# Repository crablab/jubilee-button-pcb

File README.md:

# jubilee-button-pcb

PCB for the Jubilee Line button replacement PCB. 

Created using KiCad

Check out some sample code here: https://github.com/willfurnell/jubilee-hue

Based on the [original by Will Furnell](https://github.com/willfurnell/jubilee-button-pcb). 

Released under the [MIT Licence](LICENSE). 

You should simply be able to send this off to JLCPCB for manufacture if you wish.

Or, [contact me](mailto:hugh@crablab.uk) as I have some boards already produced.

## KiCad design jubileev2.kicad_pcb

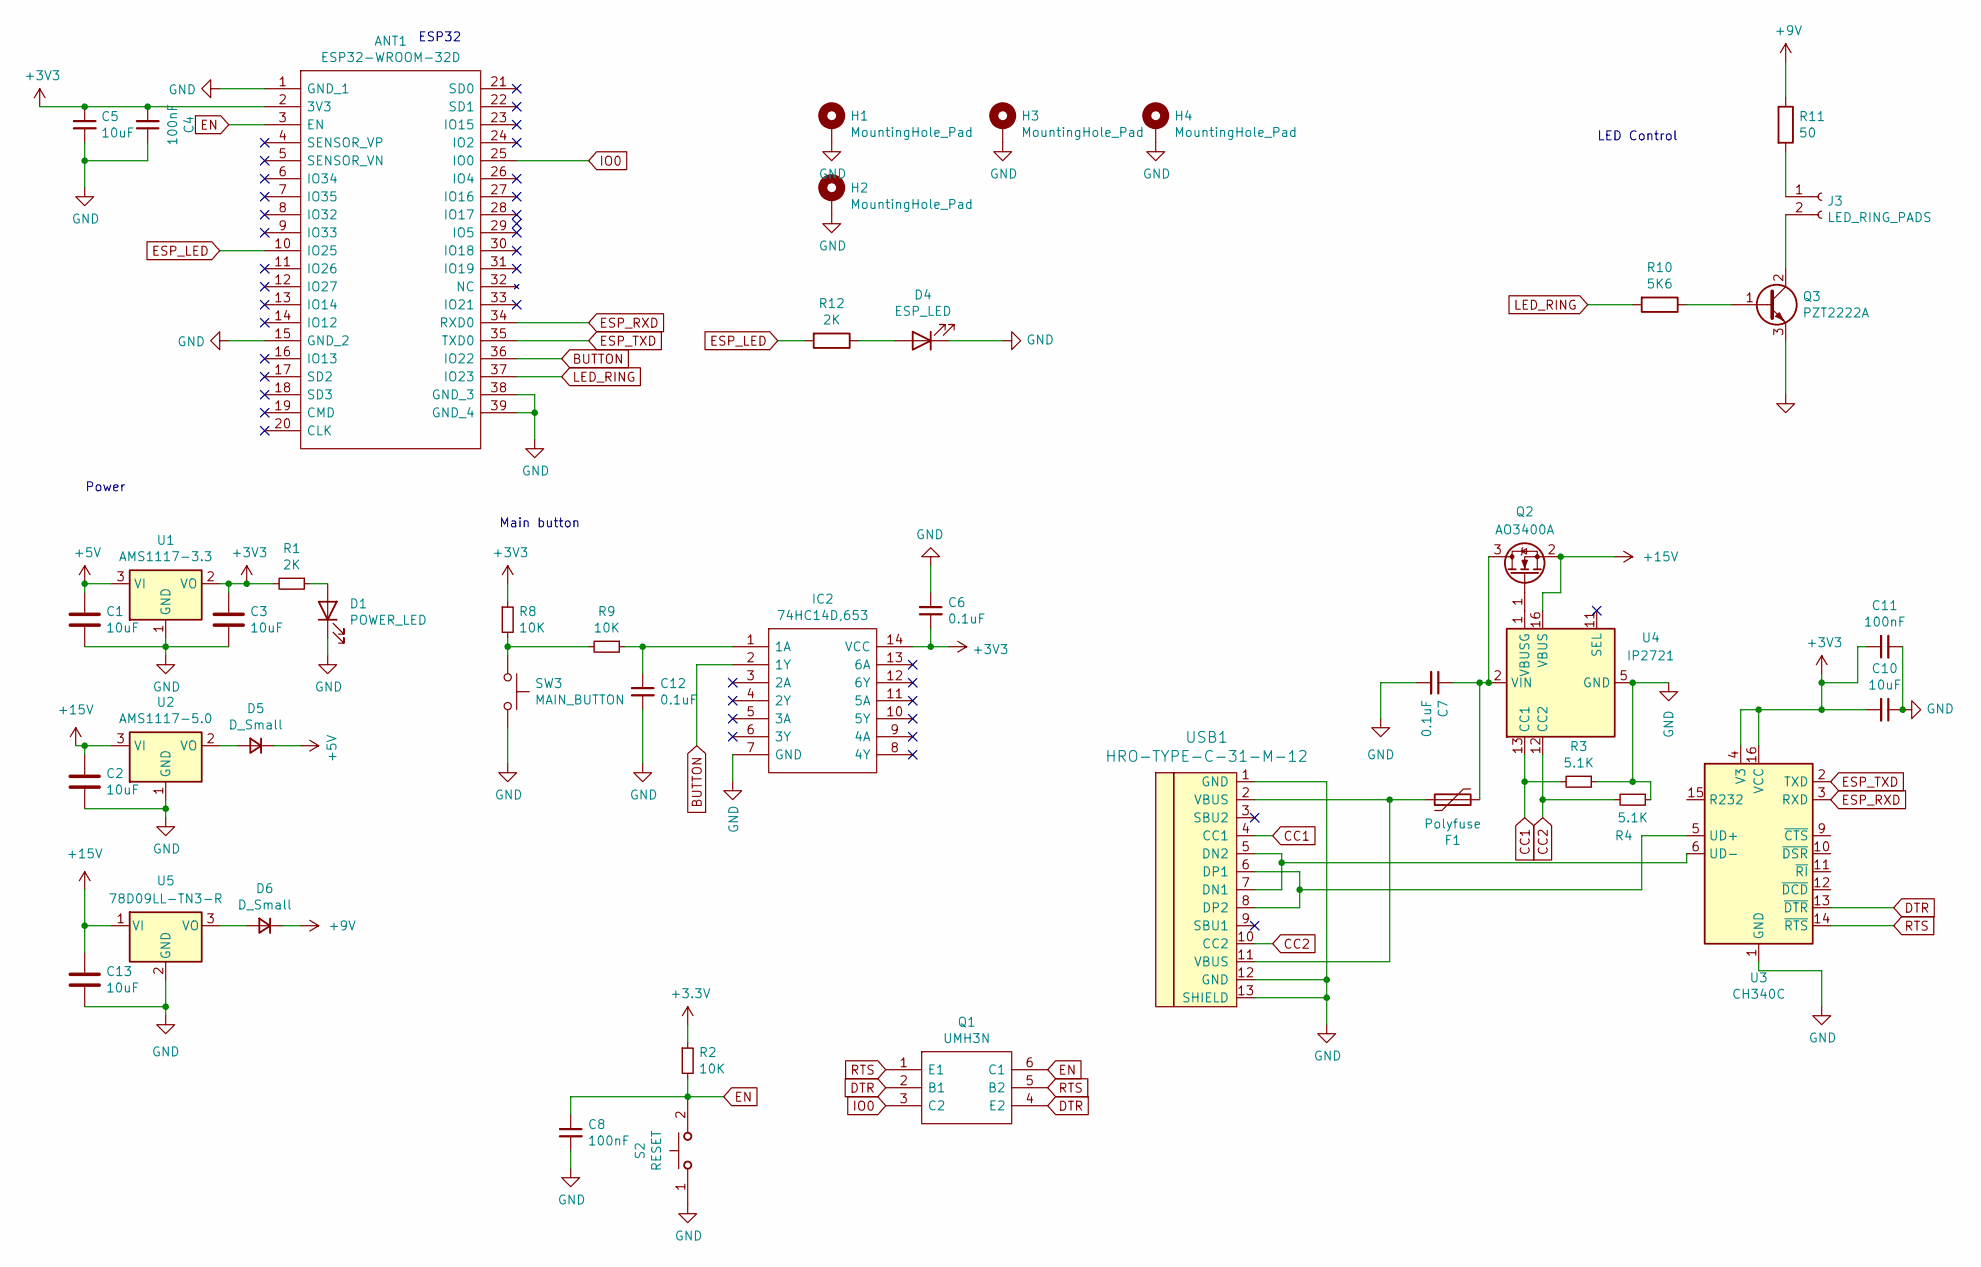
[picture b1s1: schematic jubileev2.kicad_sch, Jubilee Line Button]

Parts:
ANT1: ESP32-WROOM-32D; ESP32WROOM32D; Manufacturer_Part_Number ESP32-WROOM-32D; Mouser Part Number N/A
C1, C2, C3, C5, C10, C13: 10uF; C_0805_2012Metric
C4, C8, C11: 100nF; C_0805_2012Metric
C6, C7, C12: 0.1uF; C_0805_2012Metric
D1: POWER_LED; LED_0805_2012Metric
D4: ESP_LED; LED_0805_2012Metric
D5, D6: D_Small; D_SOD-123
F1: Polyfuse; Fuse_1206_3216Metric
H1, H2, H3, H4: MountingHole_Pad; MountingHole_3.5mm_Pad_TopBottom
IC2: 74HC14D,653; SOIC127P600X175-14N; Manufacturer_Part_Number 74HC14D,653; Mouser Part Number 771-74HC14D-T
J3: LED_RING_PADS; SolderWire-0.5sqmm_1x02_P4.6mm_D0.9mm_OD2.1mm
Q1: UMH3N; SOT65P230X110-6N; Manufacturer_Part_Number UMH3N
Q2: AO3400A; SOT-23
Q3: PZT2222A; SOT-223-3_TabPin2
R1, R12: 2K; R_0805_2012Metric
R2, R8, R9: 10K; R_0805_2012Metric
R3, R4: 5.1K; R_0805_2012Metric
R10: 5K6; R_0805_2012Metric
R11: 50; R_0805_2012Metric
S2: RESET; FSM2JRT; Mouser Part Number 506-FSM2JRT
SW3: MAIN_BUTTON; SolderWire-0.5sqmm_1x02_P4.6mm_D0.9mm_OD2.1mm
U1: AMS1117-3.3; SOT-223-3_TabPin2
U2: AMS1117-5.0; SOT-223-3_TabPin2
U3: CH340C; SOIC-16_3.9x9.9mm_P1.27mm
U4: IP2721; TSSOP-16_4.4x5mm_P0.65mm
U5: 78D09LL-TN3-R; TO-252-2
USB1: HRO-TYPE-C-31-M-12

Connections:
+5V: C1.1, D5.1 (K), U1.3 (VI)
+9V: D6.1 (K), R11.1
+15V: C2.1, C13.1, Q2.2 (S), U2.3 (VI), U4.16 (VBUS), U5.1 (VI)
BUTTON: ANT1.36 (IO22), IC2.2 (1Y)
CC1: R3.2, U4.13 (CC1), USB1.4 (CC1)
CC2: R4.2, U4.12 (CC2), USB1.10 (CC2)
DTR: Q1.2 (B1), Q1.4 (E2), U3.13 (~DTR)
EN: ANT1.3 (EN), C8.1, Q1.6 (C1), R2.2, S2.2
ESP_LED: ANT1.10 (IO25), R12.2
ESP_RXD: ANT1.34 (RXD0), U3.3 (RXD)
ESP_TXD: ANT1.35 (TXD0), U3.2 (TXD)
GND: ANT1.1 (GND_1), ANT1.15 (GND_2), ANT1.38 (GND_3), ANT1.39 (GND_4), C1.2, C2.2, C3.2, C4.1, C5.2, C6.1, C7.2, C8.2, C10.1, C11.2, C12.2, C13.2, D1.1 (K), D4.1 (K), H1.1, H2.1, H3.1, H4.1, IC2.7 (GND), Q3.3 (E), R3.1, R4.1, S2.1, SW3.2, U1.1 (GND), U2.1 (GND), U3.1 (GND), U4.5 (GND), U5.2 (GND), USB1.1 (GND), USB1.12 (GND), USB1.13 (SHIELD)
IO0: ANT1.25 (IO0), Q1.3 (C2)
LED_RING: ANT1.37 (IO23), R10.2
unnamed: D1.2 (A), R1.1
unnamed: D4.2 (A), R12.1
unnamed: D5.2 (A), U2.2 (VO)
unnamed: D6.2 (A), U5.3 (VO)
unnamed: F1.1, USB1.2 (VBUS), USB1.11 (VBUS)
unnamed: C12.1, IC2.1 (1A), R9.1
unnamed: J3.1, R11.2
unnamed: J3.2, Q3.2 (C)
unnamed: C7.1, F1.2, Q2.3 (D), U4.2 (VIN)
unnamed: Q2.1 (G), U4.1 (VBUSG)
unnamed: Q3.1 (B), R10.1
unnamed: R8.2, R9.2, SW3.1
unnamed: U3.5 (UD+), USB1.6 (DP1), USB1.8 (DP2)
unnamed: U3.6 (UD-), USB1.5 (DN2), USB1.7 (DN1)
RTS: Q1.1 (E1), Q1.5 (B2), U3.14 (~RTS)

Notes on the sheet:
Main button
ESP32
Power
LED Control

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
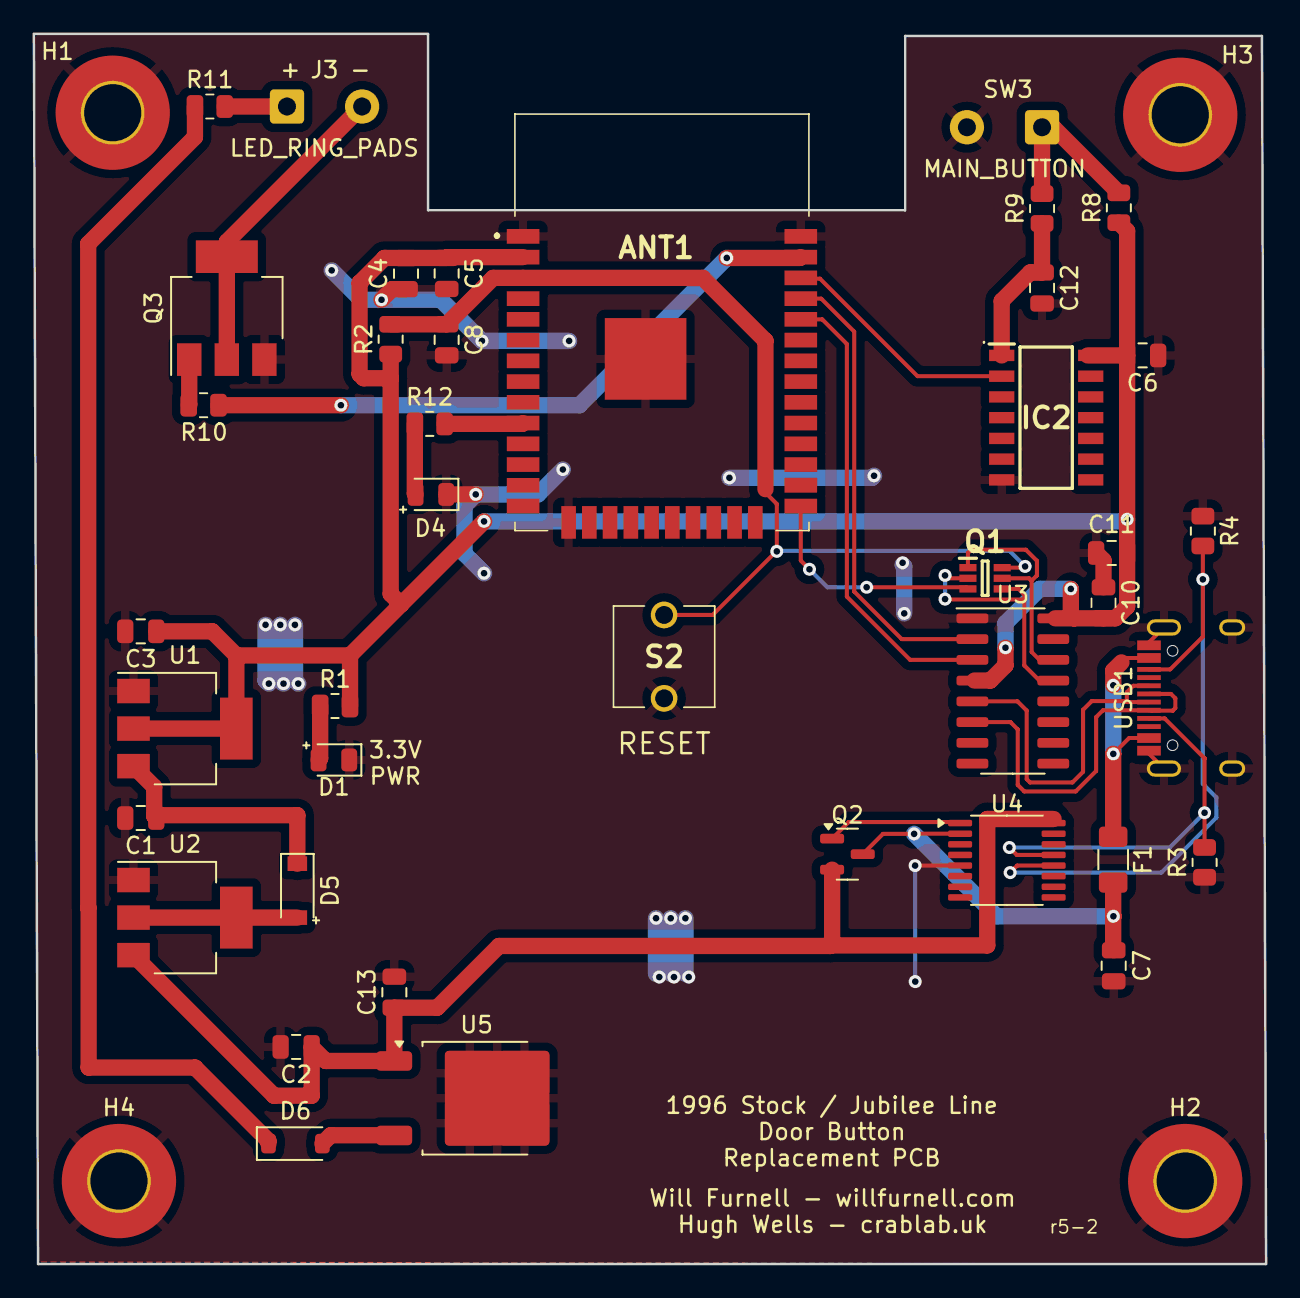
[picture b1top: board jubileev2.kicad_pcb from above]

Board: 2 copper layers, 75.4 x 75.3 mm, 44 parts (0 on the bottom side), 30 nets.

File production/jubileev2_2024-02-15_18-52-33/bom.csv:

Designator,Footprint,Quantity,Value,LCSC Part #
ANT1,ESP32WROOM32D,1,ESP32-WROOM-32D,
"C1, C10, C2, C3, C5",0805,5,10uF,
"C11, C4, C8",0805,3,100nF,
"C12, C6",0805,2,0.1uF,
D1,0805,1,POWER_LED,
D2,D_SOD-123,1,D_Schottky,
D3,D_SOD-123,1,D,
D4,0805,1,ESP_LED,
D5,D_SOD-123,1,D_Small,
F1,1206,1,Polyfuse,
IC2,SOIC127P600X175-14N,1,"74HC14D,653",
J1,Barrel_Jack_5.5mmODx2.1mmID_PJ-202A,1,PJ-202A,
Q1,SOT65P230X110-6N,1,UMH3N,
Q3,SOT-223-3_TabPin2,1,PZT2222A,
"R1, R12",0805,2,2K,
R10,0805,1,5K6,
R11,0805,1,50,
"R2, R8, R9",0805,3,10K,
"R3, R4",0805,2,5.1K,
S2,FSM2JRT,1,RESET,
U1,SOT-223-3_TabPin2,1,AMS1117-3.3,
U2,SOT-223-3_TabPin2,1,AMS1117-5.0,
U3,SOIC-16_3.9x9.9mm_P1.27mm,1,CH340C,
USB1,HRO-TYPE-C-31-M-12,1,HRO-TYPE-C-31-M-12,

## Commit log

2024-10-06 Update PCB with new USB-C PD power supply
2024-10-06 Remove files from previous iterations
2024-10-06 Update fabrication outputs
